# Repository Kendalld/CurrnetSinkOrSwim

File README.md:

# CurrnetSinkOrSwim
Contextual electronics current supply project

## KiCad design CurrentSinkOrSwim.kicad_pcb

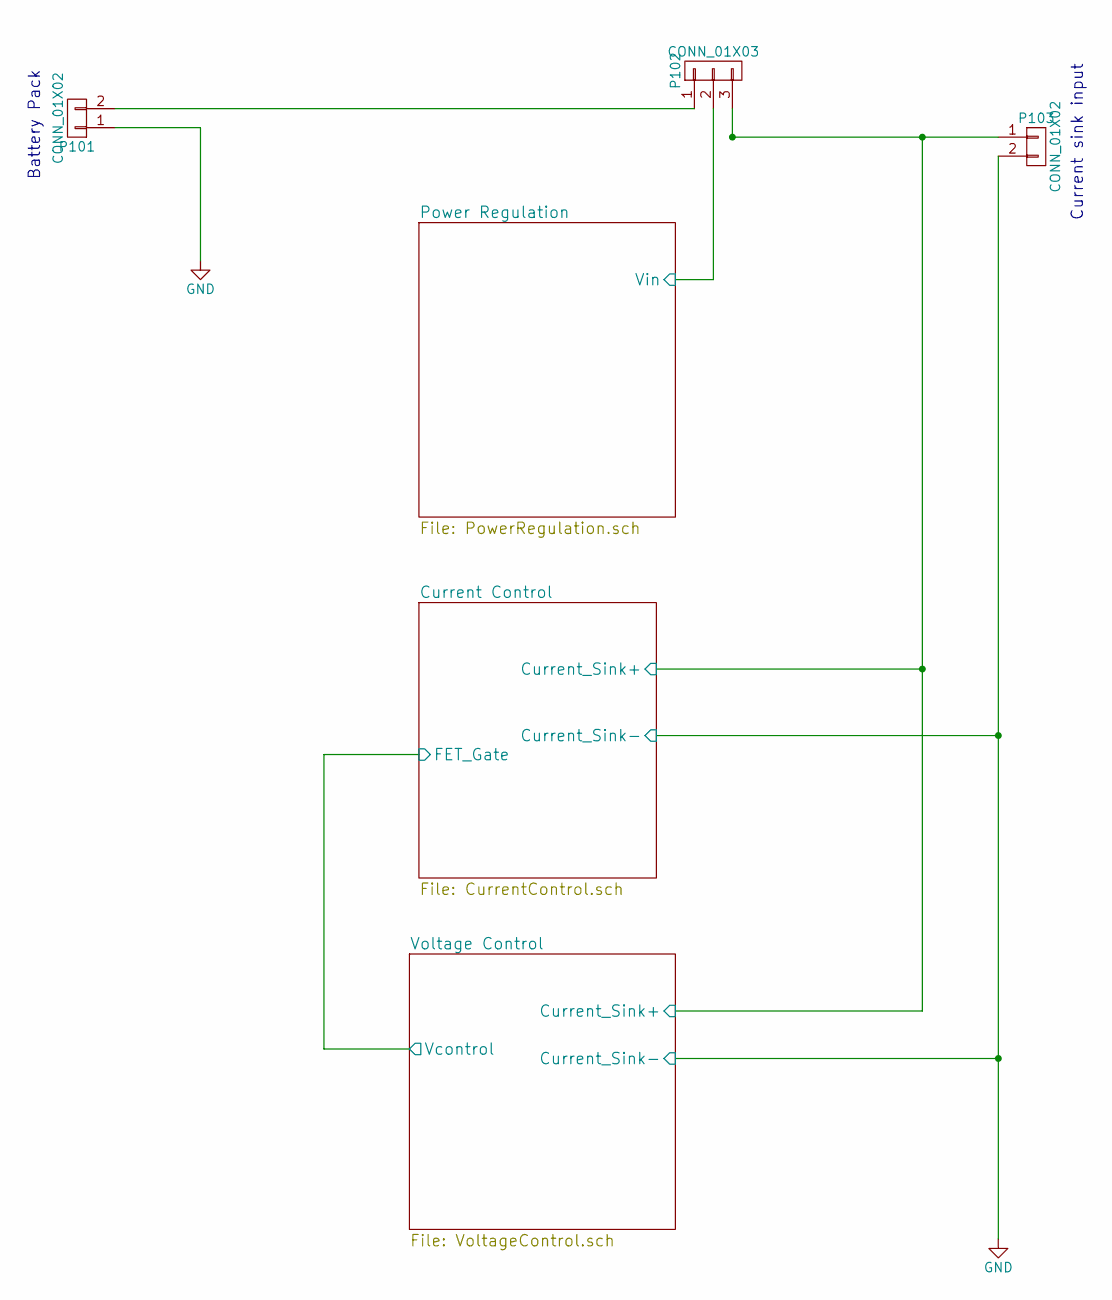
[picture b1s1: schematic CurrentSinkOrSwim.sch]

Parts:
P101, P103: CONN_01X02; AK300-2; MPN OSTTC022162
P102: CONN_01X03; Pin_Header_Straight_1x03

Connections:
/Current Control/Current_Sink+: P102.3, P103.1; also elsewhere on the board
/Power Regulation/Vin: P102.2; also elsewhere on the board
GND: P101.1, P103.2; also elsewhere on the board
unnamed: P101.2, P102.1

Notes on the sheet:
Battery Pack
Current sink input

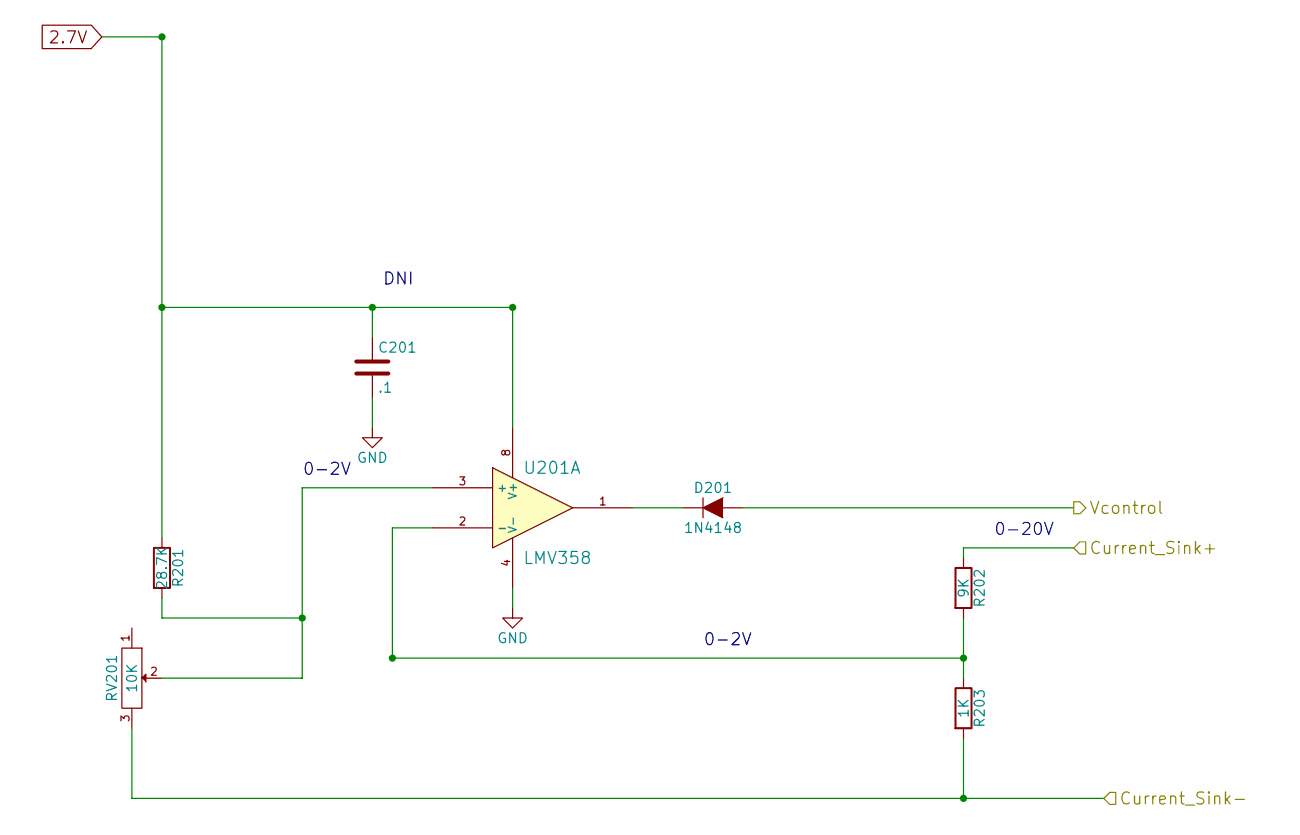
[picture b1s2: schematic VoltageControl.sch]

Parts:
C201: .1; C_0805_HandSoldering
D201: 1N4148; SOD-123; MPN 1N4148WT-7
R201: 28.7K; R_0805_HandSoldering; MPN Value
R202: 9K; R_0805_HandSoldering
R203: 1K; R_0805_HandSoldering; MPN Value
RV201: 10K; P090L-02F25BR10K; MPN P090L-02F25BR10K
U201: LMV358; SOIC-8-N; MPN LMV358IDT

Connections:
2.7V: C201.1, R201.1, U201.8 (V+); also elsewhere on the board
/Current Control/Current_Sink+: R202.1; also elsewhere on the board
/Current Control/FET_Gate: D201.2 (A); also elsewhere on the board
GND: C201.2, R203.2, RV201.3, U201.4 (V-); also elsewhere on the board
unnamed: D201.1 (K), U201.1
unnamed: R201.2, RV201.2, U201.3 (+)
unnamed: R202.2, R203.1, U201.2 (-)

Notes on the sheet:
0-2V
0-20V
DNI

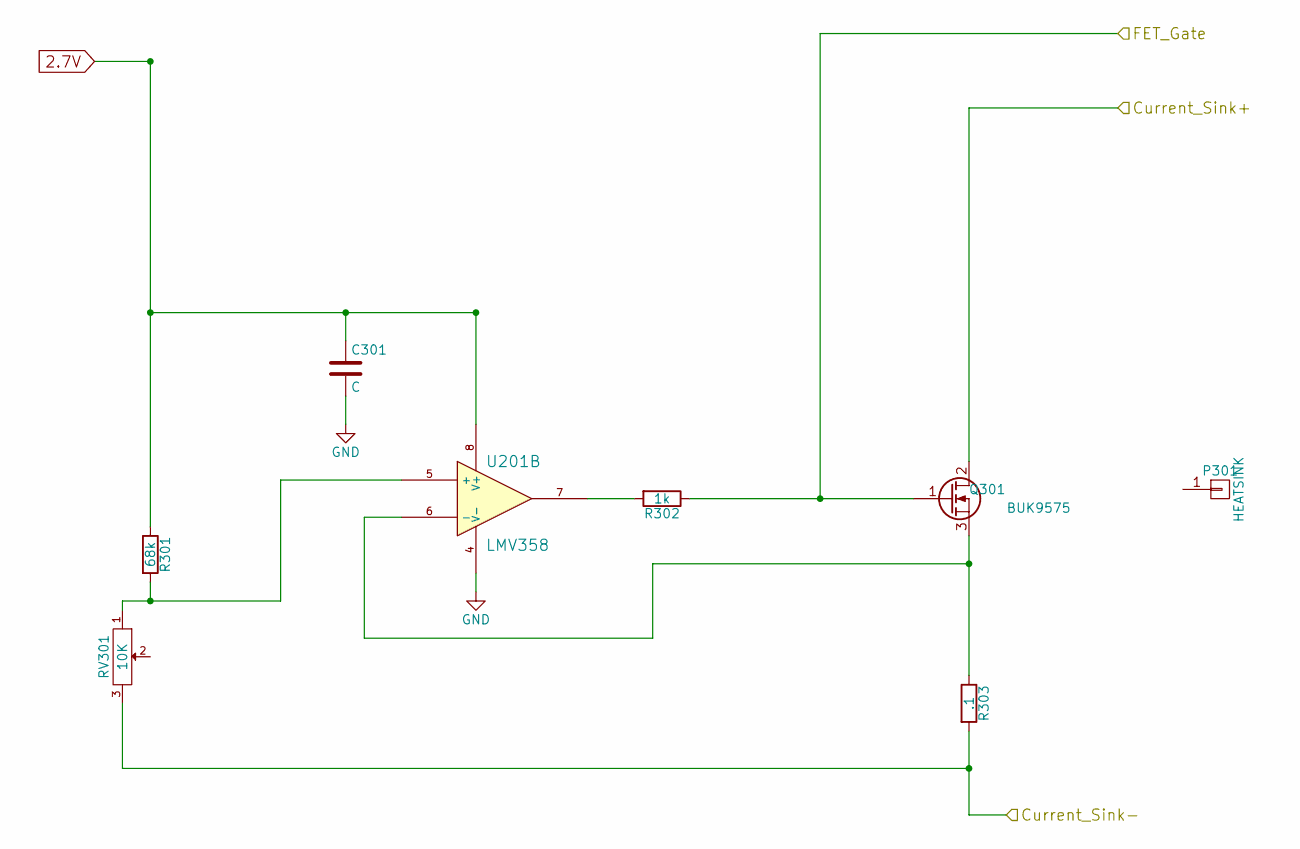
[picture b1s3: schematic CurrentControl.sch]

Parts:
C301: C; C_0805_HandSoldering
P301: HEATSINK; FA-T220-38E; MPN FA-T220-38E-ND
Q301: BUK9575; TO-220_GDS_Vertical; MPN BUK9575-100A,127
R301: 68k; R_0805_HandSoldering
R302: 1k; R_0805_HandSoldering
R303: .1; Resistor_Horizontal_RM15mm; MPN AC01000001007JA100
RV301: 10K; P090L-02F25BR10K; MPN P090L-02F25BR10K
U201: LMV358; SOIC-8-N; MPN LMV3581DT

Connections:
2.7V: C301.1, R301.1, U201.8 (V+); also elsewhere on the board
/Current Control/Current_Sink+: Q301.2 (D); also elsewhere on the board
/Current Control/FET_Gate: Q301.1 (G), R302.1; also elsewhere on the board
GND: C301.2, R303.2, RV301.3, U201.4 (V-); also elsewhere on the board
unnamed: Q301.3 (S), R303.1, U201.6 (-)
unnamed: R301.2, RV301.1, U201.5 (+)
unnamed: R302.2, U201.7

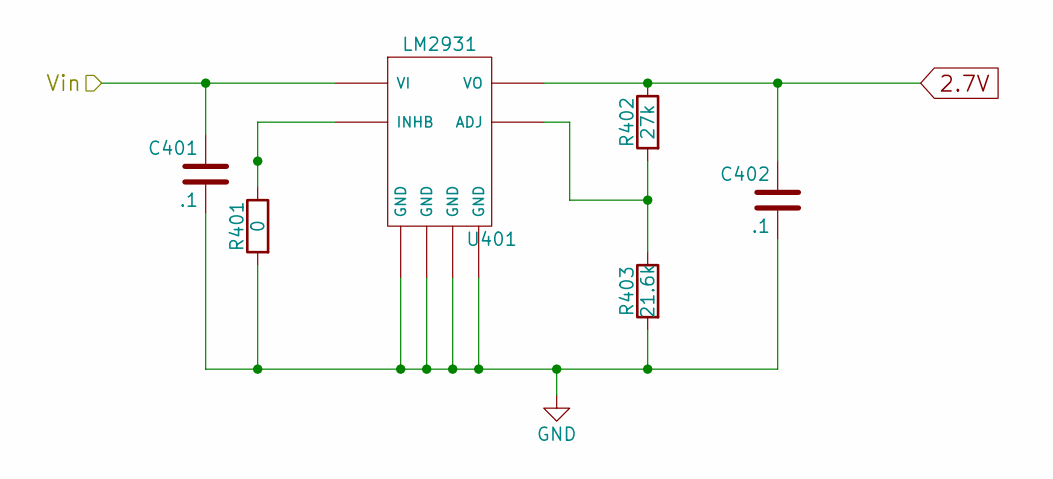
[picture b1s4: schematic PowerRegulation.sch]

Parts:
C401, C402: .1; C_0805_HandSoldering
R401: 0; R_0805_HandSoldering
R402: 27k; R_0805_HandSoldering
R403: 21.6k; R_0805_HandSoldering
U401: LM2931; SOIC-8-N; MPN LM2931D-R

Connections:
2.7V: C402.1, R402.1, U401.1 (VO); also elsewhere on the board
/Power Regulation/Vin: C401.1, U401.8 (VI); also elsewhere on the board
GND: C401.2, C402.2, R401.2, R403.2, U401.2 (GND), U401.3 (GND), U401.6 (GND), U401.7 (GND); also elsewhere on the board
unnamed: R401.1, U401.5 (INHB)
unnamed: R402.2, R403.1, U401.4 (ADJ)

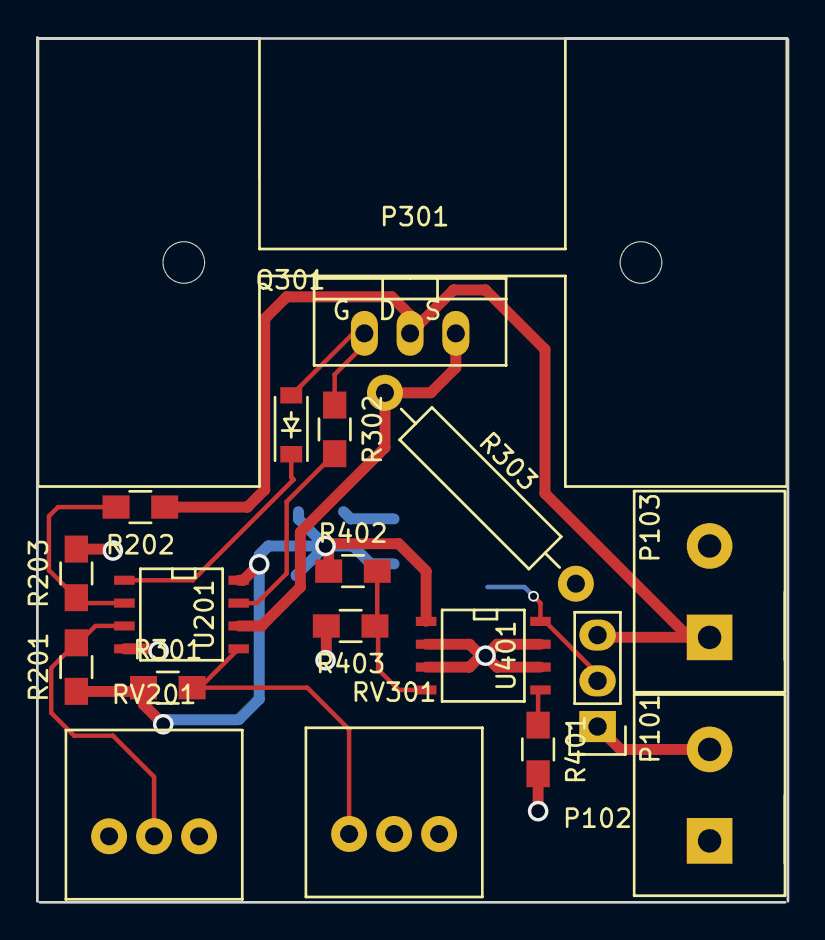
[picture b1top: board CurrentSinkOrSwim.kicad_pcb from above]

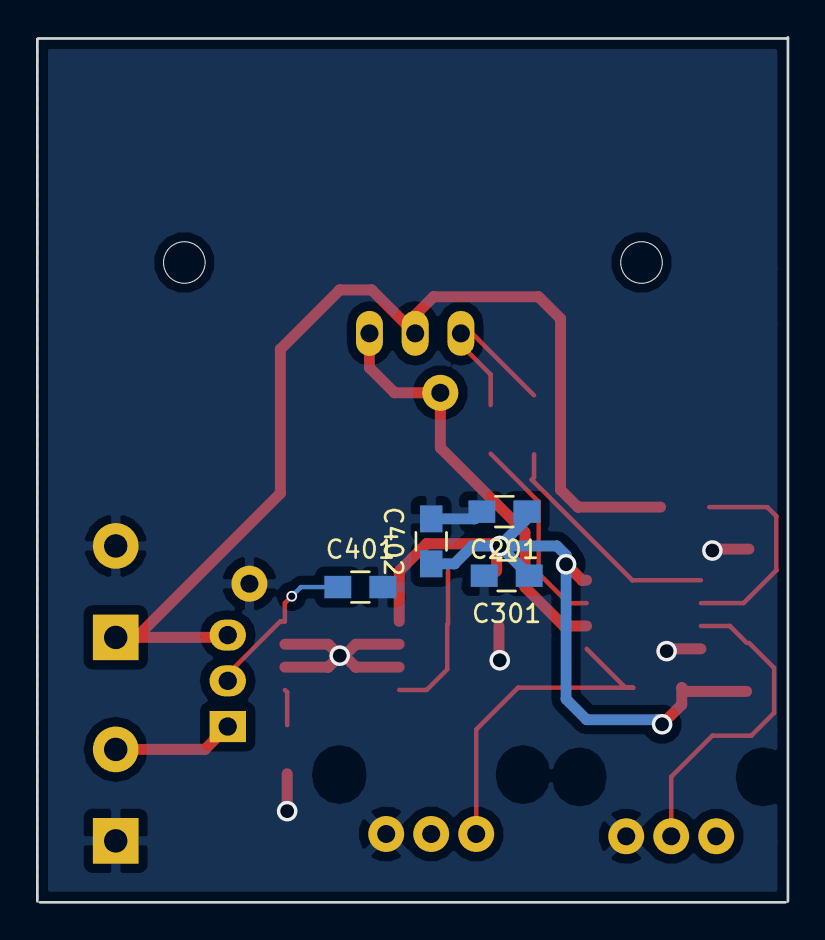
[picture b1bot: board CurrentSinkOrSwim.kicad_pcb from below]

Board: 2 copper layers, 41.7 x 48.1 mm, 23 parts (4 on the bottom side), 14 nets.

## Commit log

2015-11-15 KiCad project and Schematic creation
2015-11-16 Adding .gitignore for bakup and data files
2015-11-17 Added 2 more rules to .gitignore file
2015-12-08 Adding preliminary values to the componenets
2016-01-25 Added Hierarchical File
2016-01-25 Added Power Regulation schematic
2016-01-25 Added Current Sink or Swim Schematic Hierarchy Sheet
2016-01-25 Annotated sheets
2016-02-29 Updated BOM
2016-03-01 This is the version of the file that has been submitted to OSH park
